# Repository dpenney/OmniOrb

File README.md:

# OmniOrb

A multi-functional, high-performance interactive hub for the [Waveshare ESP32-S3-Knob-Touch-LCD-1.28](https://www.waveshare.com/esp32-s3-knob-touch-lcd-1.28.htm). 

**OmniOrb** is the next iteration of the [waveshare_radar_blipper](https://github.com/dpenney/waveshare_radar_blipper) project, expanded into a comprehensive "desktop companion" that integrates real-time data, AI assistance, and high-end visuals.

## 🚀 Features

-   **📡 ADSB Radar:** Real-time PPI-style aircraft tracking with smooth sweep animations. Painted blips and touch-to-view details.
-   **🕒 Smart Clock:** A high-frequency, smooth-beat digital/analog hybrid clock with anti-aliasing.
-   **🤖 NEXUS Assistant:** An AI-powered voice assistant with a futuristic "iris" UI, powered by a Raspberry Pi backend using Google Gemini.
-   **⚙️ Twin-Core Architecture:** Seamless synchronization between the ESP32 (display/UI) and the Raspberry Pi (AI "brains" and audio processing).
-   **🕹️ Interactive Controls:** Full support for the mechanical rotary encoder and touch gestures.

## 📁 Project Structure

```bash
├── pi/                 # Raspberry Pi backend (Python, AI Brains, Audio)
│   ├── install.sh      # Robust "one-click" installer for the Pi
│   ├── assistant_brains.py
│   └── setup_adsb.sh   # 1090-fa setup script
├── src/                # ESP32 Firmware (C++, LVGL)
│   ├── AssistantView.cpp
│   ├── ClockView.cpp
│   └── main.cpp
├── include/            # Hardware & WiFi configuration
└── platformio.ini      # Build configuration
```

## 🛠️ Setup & Installation

Detailed instructions for both the ESP32 and the Raspberry Pi side can be found in the [SETUP_GUIDE.md](pi/SETUP_GUIDE.md).

1.  **Pi Backend:** Use the provided `pi/install.sh` for an automated setup of services and dependencies.
2.  **ESP32 Firmware:** Flash using PlatformIO. Ensure your `include/config.h` is set up with your WiFi and Pi IP.

## 📜 Credits & History

This project began as a dedicated ADS-B radar display. It has since evolved into a generalized multi-app hub for round displays. 

Original repository: [dpenney/waveshare_radar_blipper](https://github.com/dpenney/waveshare_radar_blipper)

## ⚖️ License

MIT

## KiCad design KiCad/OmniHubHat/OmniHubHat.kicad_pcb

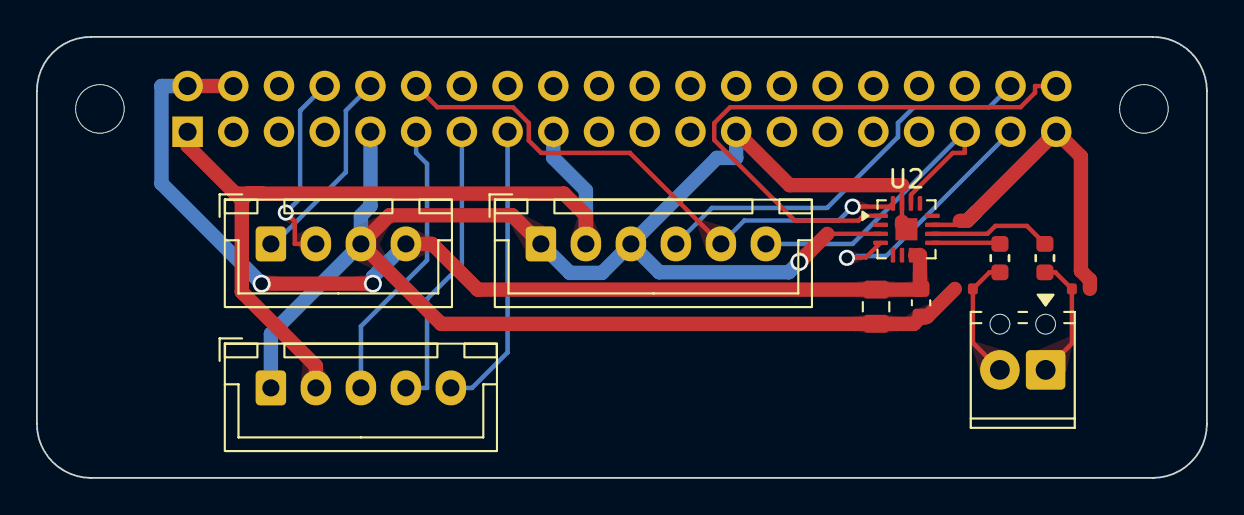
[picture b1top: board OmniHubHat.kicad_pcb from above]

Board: 2 copper layers, 65.0 x 24.5 mm, 14 parts (1 on the bottom side), 17 nets.

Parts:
C2: .1uF; C_0603_1608Metric
C3: 10uF; C_0805_2012Metric
C4, C5: 1nF; C_0402
ESP_32: UART_PWR; JST_XH_B4B-XH-A_1x04_P2.50mm_Vertical
FB1, FB2: FB_0603
I2S_Microphone1: I2S Microphone; JST_XH_B6B-XH-A_1x06_P2.50mm_Vertical
J1: GPIO; PinSocket_2x20_P2.54mm_Vertical
J2: Screw_Terminal_01x02; TerminalBlock_Phoenix_MPT-0,5-2-2.54_1x02_P2.54mm_Horizontal
MH1, MH2: MountingHole_2.7mm_M2.5
Rotary_Encoder1: Conn_01x05_Pin; JST_XH_B5B-XH-A_1x05_P2.50mm_Vertical
U2: MAX98357A; TQFN-16-1EP_3x3mm_P0.5mm_EP1.23x1.23mm

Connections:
+3V3: I2S_Microphone1.2, J1.1, J1.17, Rotary_Encoder1.2
+5V: C2.2, C3.2, ESP_32.4, J1.2, J1.4, U2.7 (VDD), U2.8 (VDD)
/GPIO14/TXD0: ESP_32.2, J1.8
/GPIO15/RXD0: ESP_32.1, J1.10
/GPIO17: J1.11, Rotary_Encoder1.3
/GPIO18/PCM.CLK: I2S_Microphone1.5, J1.12, U2.16 (BCLK)
/GPIO19/PCM.FS: I2S_Microphone1.6, J1.35, U2.14 (LRCLK)
/GPIO20/PCM.DIN: I2S_Microphone1.4, J1.38
/GPIO21/PCM.DOUT: J1.40, U2.1 (DIN)
/GPIO22: J1.15, Rotary_Encoder1.5
/GPIO26: J1.37, U2.4 (~SD_MODE)
/GPIO27: J1.13, Rotary_Encoder1.4
GND: C2.1, C3.1, C4.2, C5.1, ESP_32.3, I2S_Microphone1.1, I2S_Microphone1.3, J1.6, J1.9, J1.14, J1.20, J1.25, J1.30, J1.34, J1.39, Rotary_Encoder1.1, U2.3 (GND), U2.11 (GND), U2.15 (GND), U2.17 (PAD)
unnamed: C4.1, FB2.2, J2.1
unnamed: C5.2, FB1.2, J2.2
unnamed: FB2.1, U2.10 (OUTN)
unnamed: FB1.1, U2.9 (OUTP)

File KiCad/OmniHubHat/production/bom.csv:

Designator,Footprint,Quantity,Value,LCSC Part #
C2,0603,1,.1uF,
C3,0805,1,10uF,
"C4, C5",C_0402,2,1nF,C1523
ESP_32,JST_XH_B4B-XH-A_1x04_P2.50mm_Vertical,1,UART_PWR,
"FB1, FB2",FB_0603,2,~,C14709
I2S_MICROPHONE1,JST_XH_B6B-XH-A_1x06_P2.50mm_Vertical,1,I2S Microphone,
J1,PinSocket_2x20_P2.54mm_Vertical,1,GPIO,
J2,"TerminalBlock_Phoenix_MPT-0,5-2-2.54_1x02_P2.54mm_Horizontal",1,Screw_Terminal_01x02,
ROTARY_ENCODER1,JST_XH_B5B-XH-A_1x05_P2.50mm_Vertical,1,Conn_01x05_Pin,
U2,TQFN-16-1EP_3x3mm_P0.5mm_EP1.23x1.23mm,1,MAX98357A,

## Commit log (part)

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2026-03-28 Initial commit of OmniOrb: A multi-function hub for radar, clock, and AI Assistant
2026-03-29 Implement Auto Gain Control for Spectrum and update Assistant aesthetics
2026-03-31 feat(pi): migration to 64-bit OS and penneyd user
2026-03-31 feat(esp32): assistant view and communication sync
2026-03-31 feat(pi): optimize spectrum analyzer for speech and add sync script
2026-03-31 feat(pi): integrate openwakeword and resolve audio buffer echoing
2026-04-03 Optimized Assistant: VAD, persistent audio output, and hardware mute support
2026-04-03 feat: Broadcast app mode on boot and include home coords in data fetch
    - assistant_brains.py: track radar_active flag via serial APP: messages
    - main.cpp: call notify_pi_app_mode at boot so Pi receives initial screen state
    - main.cpp: include home lat/lon as query params in ADS-B data request
    - config.h: update ADS-B endpoint host, port and path
    - sync_brain.ps1: minor cleanup and robustness improvements
2026-04-03 chore: Update sync script and gitignore
2026-04-03 feat: Add radar/start and radar/stop HTTP control routes
2026-04-06 feat: Add SettingsView, interrupt handling, and assistant logic improvements
    - src/SettingsView: new view for device settings (volume, brightness)\n- src/main.cpp: implement swipe to settings and interrupt command\n- pi/assistant_brains.py: add clean shutdown handlers and ref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
2026-04-11 Implement universal support for RPi and Particle Tachyon. Hardware detection in installer, code-driven pin init, and optional GPIO dependencies.
2026-04-11 Implement Audio Diagnostic System, STT Logging, and Voice Sync. Fixes Port 5050 conflict.
2026-04-12 Interaction Pipeline & Tiered Memory Implementation
    Features:
    - Implemented 12s Conversation Continuity window with VAD-based wake word bypass and 'Attentive' Green/Blue visuals.
    - Integrated MemoryManager with 32k-token threshold caching and 'Barksdale' safety fallback.
    - Added volume and location synchronization to the startup boot handshake.
    - Optimized system startup with async memory seeding for sub-2s response time.
    - Fixed weather reporting bugs (WMO mapping) and redundant state-reset issues.
2026-04-29 Fix grey eyes glow when disconnected
2026-04-29 feat: Add Wi-Fi Sync, Settings Diagnostics, Globe View, and fix clock tearing
    - Wi-Fi Sync: ESP32 now acts as the central provisioning point. Upon UART connection, the ESP32 pushes its Wi-Fi credentials to the Raspberry Pi. The Pi's assistant_brains.py parses these and seamles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
    - Diagnostics UI: Added live Wi-Fi signal strength (RSSI) readouts for both the Radar (ESP32) and Brain (Pi) directly onto the Settings dial view. The Pi now fetches its actual RSSI via NetworkManage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
    - Clock Tearing Fix: Re-enabled LVGL full_refresh to force the ESP32 to DMA the entire frame sequentially, perfectly syncing with VSYNC and eliminating the horizontal tearing artifact on the se
2026-05-03 Initialize private-maint branch with full maintenance suite and private components
2026-05-03 feat: Add remote maintenance suite and logging
2026-05-03 feat: Add rotating logging to ADS-B proxy
2026-05-03 fix: Restore missing logging import
2026-05-03 feat: Implement dynamic range fetching for ADS-B radar
2026-05-03 feat: Send range parameter to ADS-B proxy
2026-05-03 Implement long-press button handling for sleep mode with debouncing
2026-05-03 feat: Wake from sleep on encoder rotation or short press
2026-05-03 feat: Scaled encoder to require 2 steps per detent
2026-05-03 debug: add request logging to adsb proxy
2026-05-04 Stabilize UI transitions and touch responsiveness
2026-05-04 Fix timer ring erase and shrinking logic
2026-05-04 Emergency: Remove leaked secrets and fix .gitignore
2026-05-04 Finalize timer ring precision and view synchronization
2026-05-04 Finalize OmniOrb interaction model: Hard-gated Radar logic, Pi-to-ESP encoder bridge, and documented interaction model in INTERACTION_MODEL.md
2026-05-04 Finalize High-Performance Iris Engine: Implemented Trig LUT and synchronized differential erase for buttery-smooth, artifact-free spectrum analyzer rendering. Added SPECTRUM_DEEP_DIVE.md documentatio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
2026-05-04 Finalize Assistant View UI Stability: Implemented Super-Wipe transition erasure and algorithm-matched solid-disc Iris rendering. Resolved all Moire artifacts and state-transition ghosting.
2026-05-07 Implement rotary encoder volume control, improved exit logic, and aircraft selection refinements
2026-05-07 Refine Settings exit logic: more robust button detection and forgiving long-press
2026-05-07 Fix globe button toggle and restore rotation tilt control
2026-05-07 Implement globe tilt control via rotary encoder (T+/T-)
2026-05-07 Fix globe tilt sensitivity: use smaller increments (0.05 rad)
2026-05-07 Remove conflicting API key environment mapping
2026-05-07 Revert API key mapping cleanup as it was working before
2026-05-07 Final fix: Restore API key mapping while preserving all new encoder features
2026-05-22 feat: add OmniHub 3MF print file to stl/
2026-06-29 feat(camera): add AI camera integration, VAD import fix, and custom pin config
2026-06-29 feat(camera): add AI camera integration, VAD and continuity optimizations
2026-06-29 feat(camera): conditionally register camera tool based on config.CAMERA_ENABLED
2026-06-29 feat(camera): conditionally register camera tool based on CAMERA_ENABLED (default to False on main)
